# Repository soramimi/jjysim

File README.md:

# jjysim

JJY（日本標準時電波、40kHz/60kHz）の時刻コードを模擬送信するためのシミュレータです。
PC または Raspberry Pi 上のソフトウェアで JJY のタイムコードを生成し、外付けハードウェア（ATtiny13 で生成したキャリア波、または PCB 基板）を変調することで、ごく近距離向けの JJY 電波を再現します。

## 構成

### `app/` — PC 用アプリケーション（Qt/C++）
- USB シリアル（FTDI 等のビットバングモード対応アダプタ）経由で外部ハードウェアの GPIO ピンを制御し、JJY のタイムコードを送出します。
- [main.cpp](app/main.cpp): 現在時刻から JJY の変調パターン（分・時・日・年・曜日・パリティを含む 60 秒分のフレーム）を生成し、シリアル経由でピンを制御して出力します。
- [serial.h](app/serial.h) / `serial.cpp`: termios ベースのシリアル通信ラッパー。
- ビルドには Qt の `qmake`（[jjysim.pro](app/jjysim.pro)）を使用します。

### `rpi/` — Raspberry Pi 用アプリケーション（C++）
- [bcm2835](https://www.airspayce.com/mikem/bcm2835/) ライブラリを使い、Raspberry Pi の GPIO を直接制御して JJY タイムコードを出力します。
- ロジックは `app/` 版とほぼ同じですが、シリアル経由ではなく GPIO を直接操作する点が異なります。
- `make` でビルドします（[Makefile](rpi/Makefile)）。

### `attiny13-firmware/` — キャリア波生成用ファームウェア（C）
- ATtiny13 上で動作し、40kHz または 60kHz の方形波キャリアを生成します。
- 入力ピンの状態でキャリア周波数の切り替えと、変調（ON/OFF）を行います。
- `make` でビルドし、`make write` で avrdude 経由で書き込みます（[Makefile](attiny13-firmware/Makefile)）。

### `pcb/` — 基板設計データ（KiCad）
- 実機ハードウェアの回路図・基板レイアウト（[jjysim.kicad_sch](pcb/jjysim.kicad_sch) / [jjysim.kicad_pcb](pcb/jjysim.kicad_pcb)）。
- `gerber/` ディレクトリに製造用の Gerber / ドリルデータを収録。

## 仕組みの概要

1. 現在時刻（年月日時分秒）から JJY のタイムコードビット列を生成し、1 秒ごとにマーカー（200ms パルス）、データ 0（800ms パルス）、データ 1（500ms パルス）のいずれかを割り当てます。
2. `app/` 版はこのパルスパターンに従って外部アダプタの GPIO ピンをシリアル経由で ON/OFF します。`rpi/` 版は同様の処理を Raspberry Pi の GPIO で直接行います。
3. GPIO 出力は ATtiny13 ファームウェアへの変調入力となり、ATtiny13 が生成する 40kHz/60kHz キャリア波をこのパルスに合わせて ON/OFF することで、JJY 標準電波と同じ形式の信号を作り出します。

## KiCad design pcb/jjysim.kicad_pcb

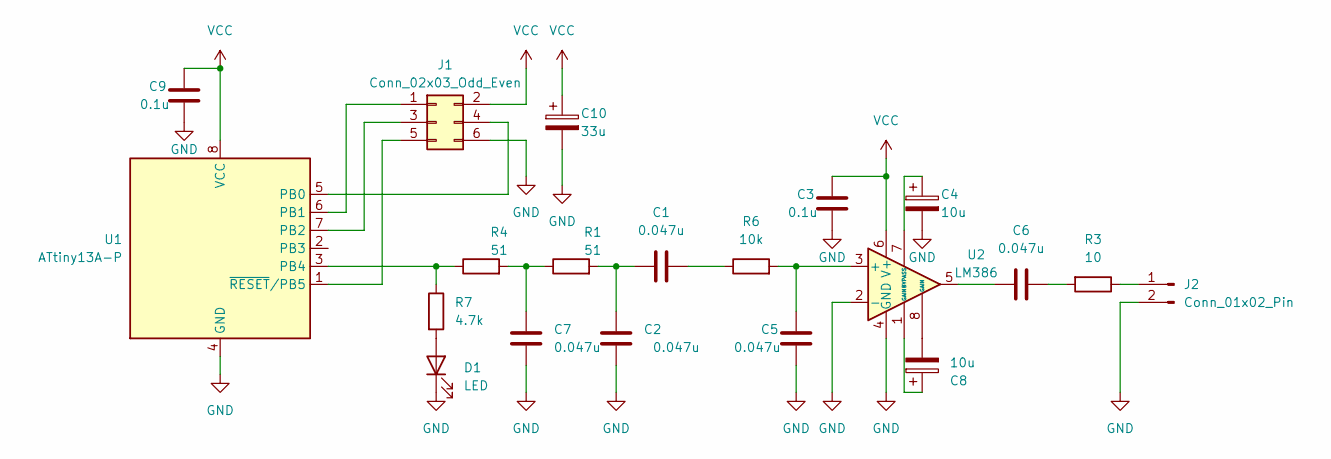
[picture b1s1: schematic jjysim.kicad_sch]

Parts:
C1, C2, C5, C6, C7: 0.047u; C_Disc_D7.5mm_W4.4mm_P5.00mm
C3, C9: 0.1u; C_Disc_D4.3mm_W1.9mm_P5.00mm
C4, C8: 10u; CP_Radial_Tantal_D5.0mm_P2.50mm
C10: 33u; CP_Radial_Tantal_D5.0mm_P2.50mm
D1: LED; LED_D3.0mm
J1: Conn_02x03_Odd_Even; PinHeader_2x03_P2.54mm_Vertical
J2: Conn_01x02_Pin; PinHeader_2x01_P2.54mm_Vertical
R1, R4: 51; R_Axial_DIN0204_L3.6mm_D1.6mm_P2.54mm_Vertical
R3: 10; R_Axial_DIN0204_L3.6mm_D1.6mm_P2.54mm_Vertical
R6: 10k; R_Axial_DIN0204_L3.6mm_D1.6mm_P2.54mm_Vertical
R7: 4.7k; R_Axial_DIN0204_L3.6mm_D1.6mm_P2.54mm_Vertical
U1: ATtiny13A-P; DIP-8_W7.62mm
U2: LM386; DIP-8_W7.62mm

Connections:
GND: C2.1, C3.1, C4.2, C5.1, C7.1, C9.1, C10.2, D1.1 (K), J1.6, J2.2, U1.4 (GND), U2.2 (-), U2.4 (GND)
unnamed: C1.1, C2.2, R1.2
unnamed: C1.2, R6.1
unnamed: C6.1, R3.2
unnamed: C6.2, U2.5
unnamed: C7.2, R1.1, R4.2
unnamed: C8.1, U2.1 (GAIN)
unnamed: C8.2, U2.8 (GAIN)
unnamed: D1.2 (A), R7.2
unnamed: J1.1, U1.6 (PB1)
unnamed: J1.3, U1.7 (PB2)
unnamed: J1.4, U1.5 (PB0)
unnamed: J1.5, U1.1 (~RESET/PB5)
unnamed: J2.1, R3.1
unnamed: R4.1, R7.1, U1.3 (PB4)
unnamed: C5.2, R6.2, U2.3 (+)
unnamed: C4.1, U2.7 (BYPASS)
VCC: C3.2, C9.2, C10.1, J1.2, U1.8 (VCC), U2.6 (V+)

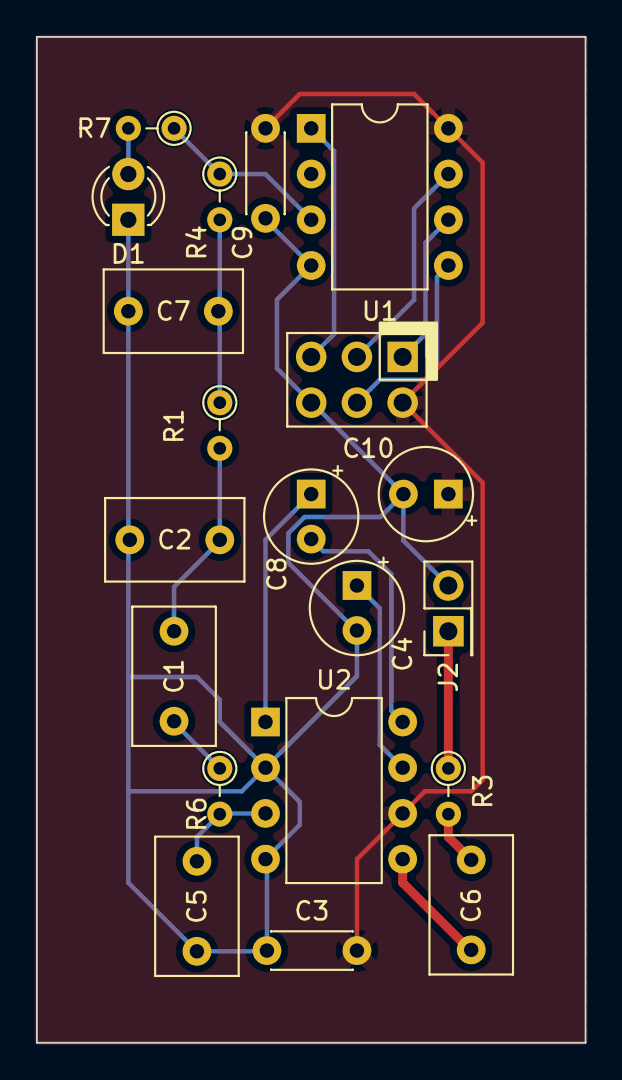
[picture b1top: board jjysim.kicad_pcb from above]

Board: 2 copper layers, 30.5 x 55.9 mm, 20 parts (0 on the bottom side), 18 nets.
